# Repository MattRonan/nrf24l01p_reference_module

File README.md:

# nrf24l01p_reference_module
nrf24l01+ board and schematic in Eagle, based on official reference board

The nrf24l01+ is cheap, well documented, and easy to use, but is way less available than it was a few years ago. I made this based on Nordic's reference module so that  
I wouldnt have to rely on amazon or ali baba suppliers in the future.  The Nordic PDF has extra info about component selection and related things, and is on their website at https://www.nordicsemi.com/Products/nRF24-series

The pdf that this board is based off of is under nRF24Files/nRF24L01P-EK/Documentation/nRF24L01pluss_REFERENCE_MODULES

There are improvements that can be made, most of all shrinking the antenna size down to match typical nrf modules but this is a good starting point

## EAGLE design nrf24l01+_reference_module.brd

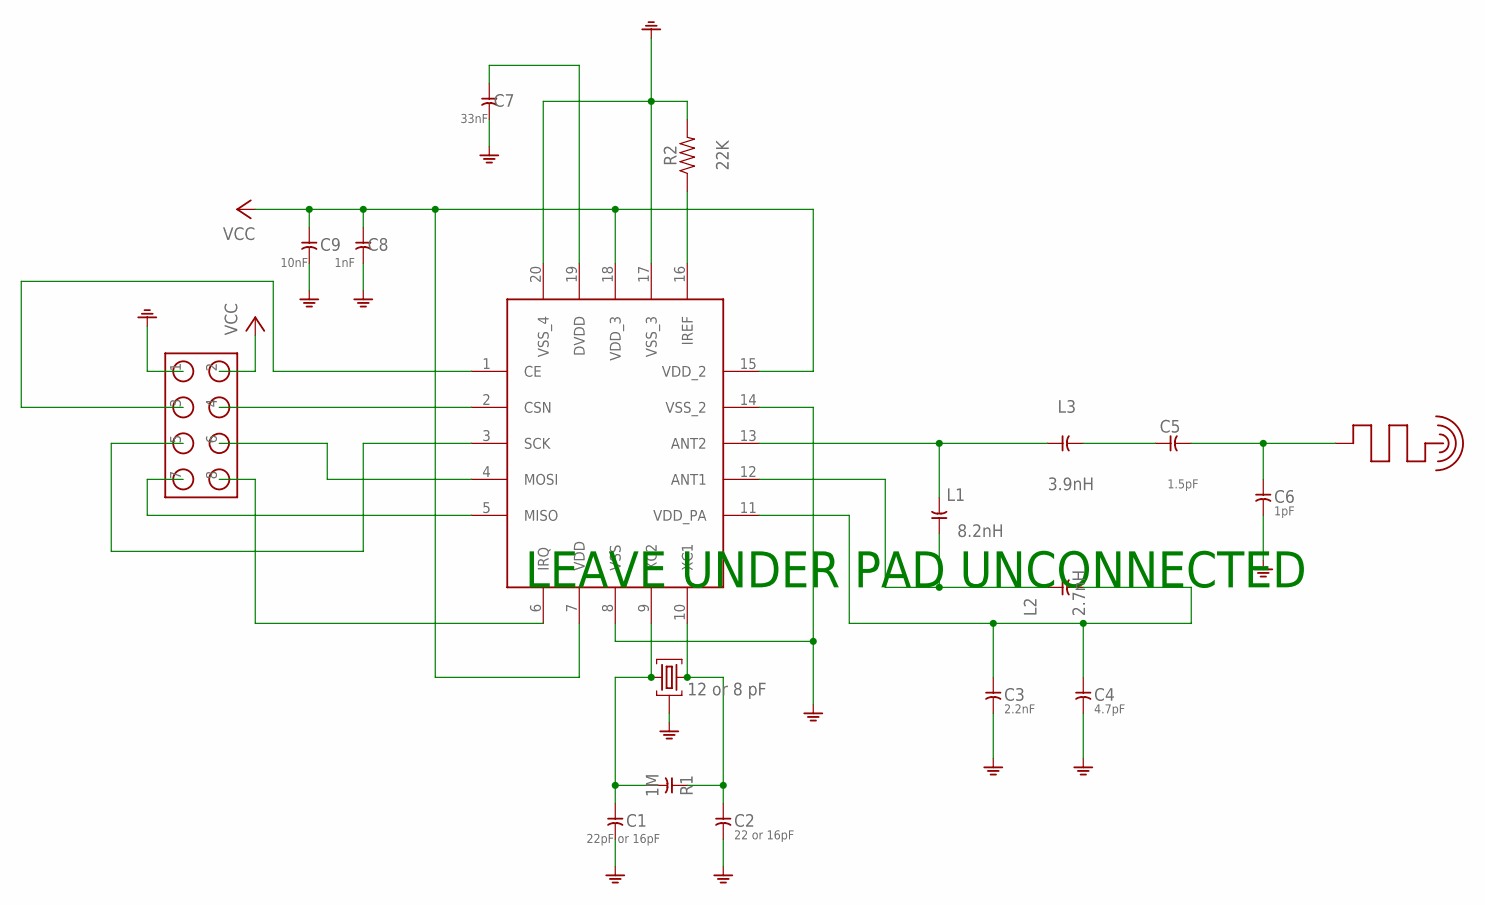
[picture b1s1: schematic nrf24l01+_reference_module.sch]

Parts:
C1: 22pF or 16pF; 0402_ULTRA_COMPACT
C2: 22 or 16pF; 0402_ULTRA_COMPACT
C3: 2.2nF; 0402_ULTRA_COMPACT
C4: 4.7pF; 0402_ULTRA_COMPACT
C5: 1.5pF; 0402_ULTRA_COMPACT
C6: 1pF; 0402_ULTRA_COMPACT
C7: 33nF; 0402_ULTRA_COMPACT
C8: 1nF; 0402_ULTRA_COMPACT
C9: 10nF; 0402_ULTRA_COMPACT
L1: 8.2nH; 0402_ULTRA_COMPACT
L2: 2.7nH; 0402_ULTRA_COMPACT
L3: 3.9nH; 0402_ULTRA_COMPACT
R1: 1M; 0402_ULTRA_COMPACT
R2: 22K; 0402_COMPACT
U$1: NRF24L01+_NO_UNDERSIDE_PAD; QFN20_4MM_NO_BOTTOM_PAD
U$2: HEADER_2X4; 2X4_2.54MM
U$4: 12 or 8 pF; CRYSTAL_SMD4_PINT_SIZE
U$5: ANTENNA_NRF_REFERENCE_MODULE

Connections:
GND: C1.2, C2.2, C3.2, C4.2, C6.2, C7.2, C8.2, C9.2, R2.2, U$1.8 (VSS), U$1.14 (VSS_2), U$1.17 (VSS_3), U$1.20 (VSS_4), U$2.1, U$4.2(GND) (GND), U$4.4(GND) (GND)
unnamed: U$1.1 (CE), U$2.3
unnamed: U$1.2 (CSN), U$2.4
unnamed: U$1.3 (SCK), U$2.5
unnamed: U$1.4 (MOSI), U$2.6
unnamed: U$1.5 (MISO), U$2.7
unnamed: U$1.6 (IRQ), U$2.8
unnamed: C1.1, R1.2, U$1.9 (XC2), U$4.1
unnamed: C2.1, R1.1, U$1.10 (XC1), U$4.3
unnamed: C7.1, U$1.19 (DVDD)
unnamed: L1.2, L3.1, U$1.13 (ANT2)
unnamed: R2.1, U$1.16 (IREF)
unnamed: L1.1, L2.1, U$1.12 (ANT1)
unnamed: C3.1, C4.1, L2.2, U$1.11 (VDD_PA)
unnamed: C5.1, L3.2
unnamed: C5.2, C6.1, U$5.P$1
VCC: C8.1, C9.1, U$1.7 (VDD), U$1.15 (VDD_2), U$1.18 (VDD_3), U$2.2

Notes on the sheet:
LEAVE UNDER PAD UNCONNECTED

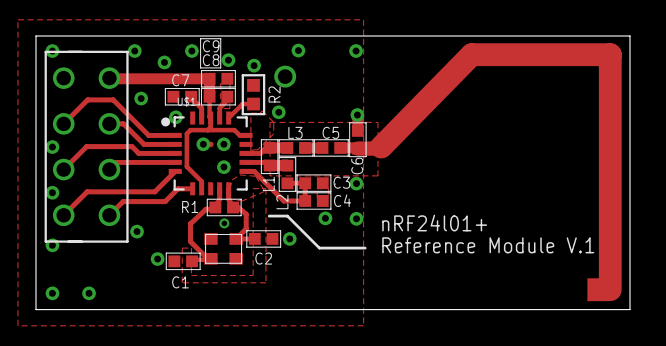
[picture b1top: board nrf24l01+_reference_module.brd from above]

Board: 2 copper layers, 33.0 x 15.2 mm, 18 parts (0 on the bottom side), 17 nets.

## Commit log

2022-02-15 Create LICENSE
